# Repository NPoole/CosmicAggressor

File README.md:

# CosmicAggressor

Badge style 'Space Invaders' clone based on the stacked-FR4 construction technique.<br/>
Processor is 32u4, LEDs are APA-102-2020 6-pin

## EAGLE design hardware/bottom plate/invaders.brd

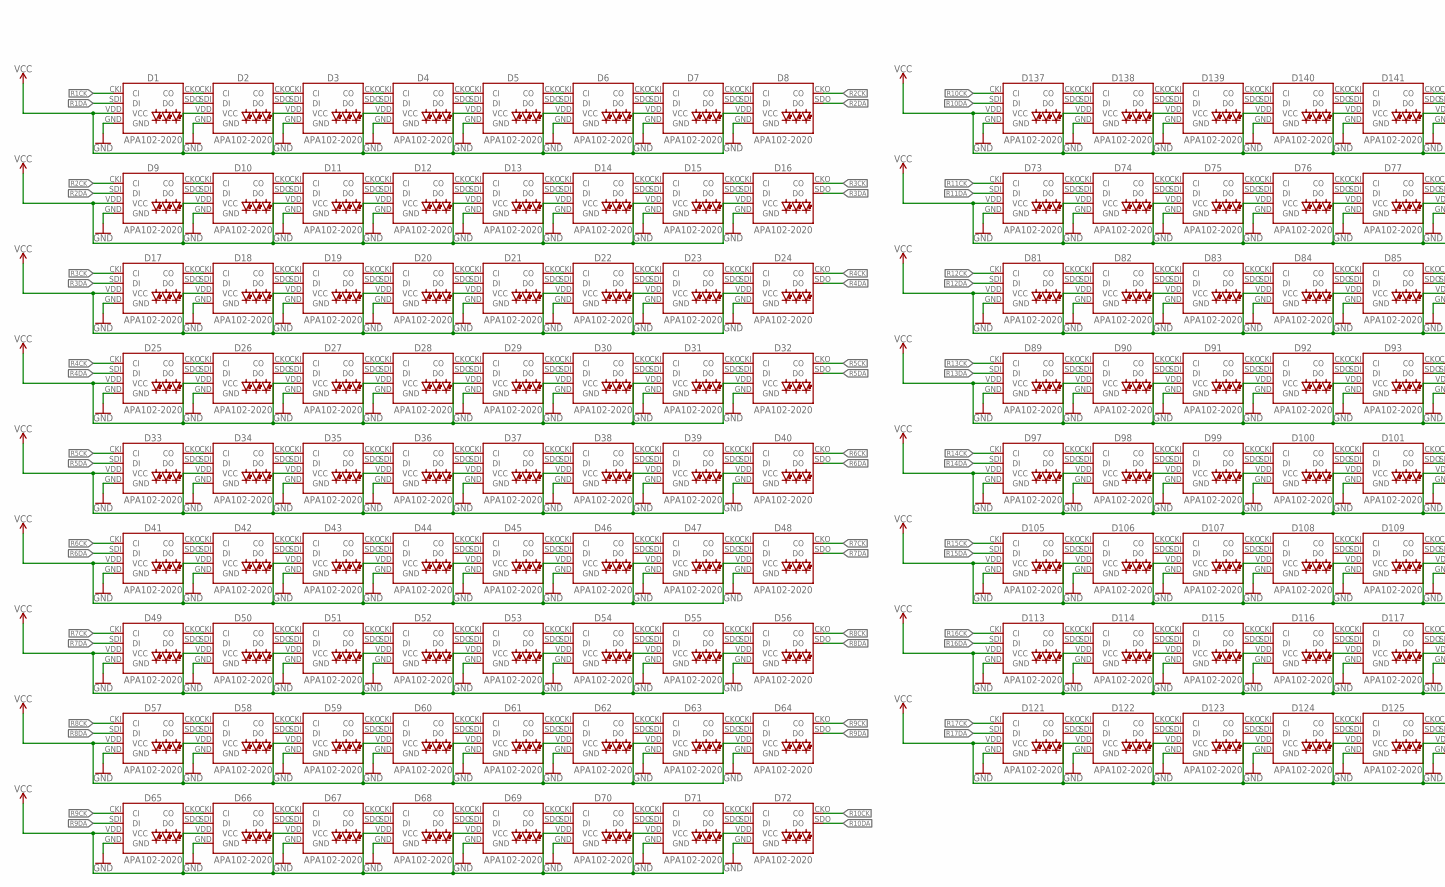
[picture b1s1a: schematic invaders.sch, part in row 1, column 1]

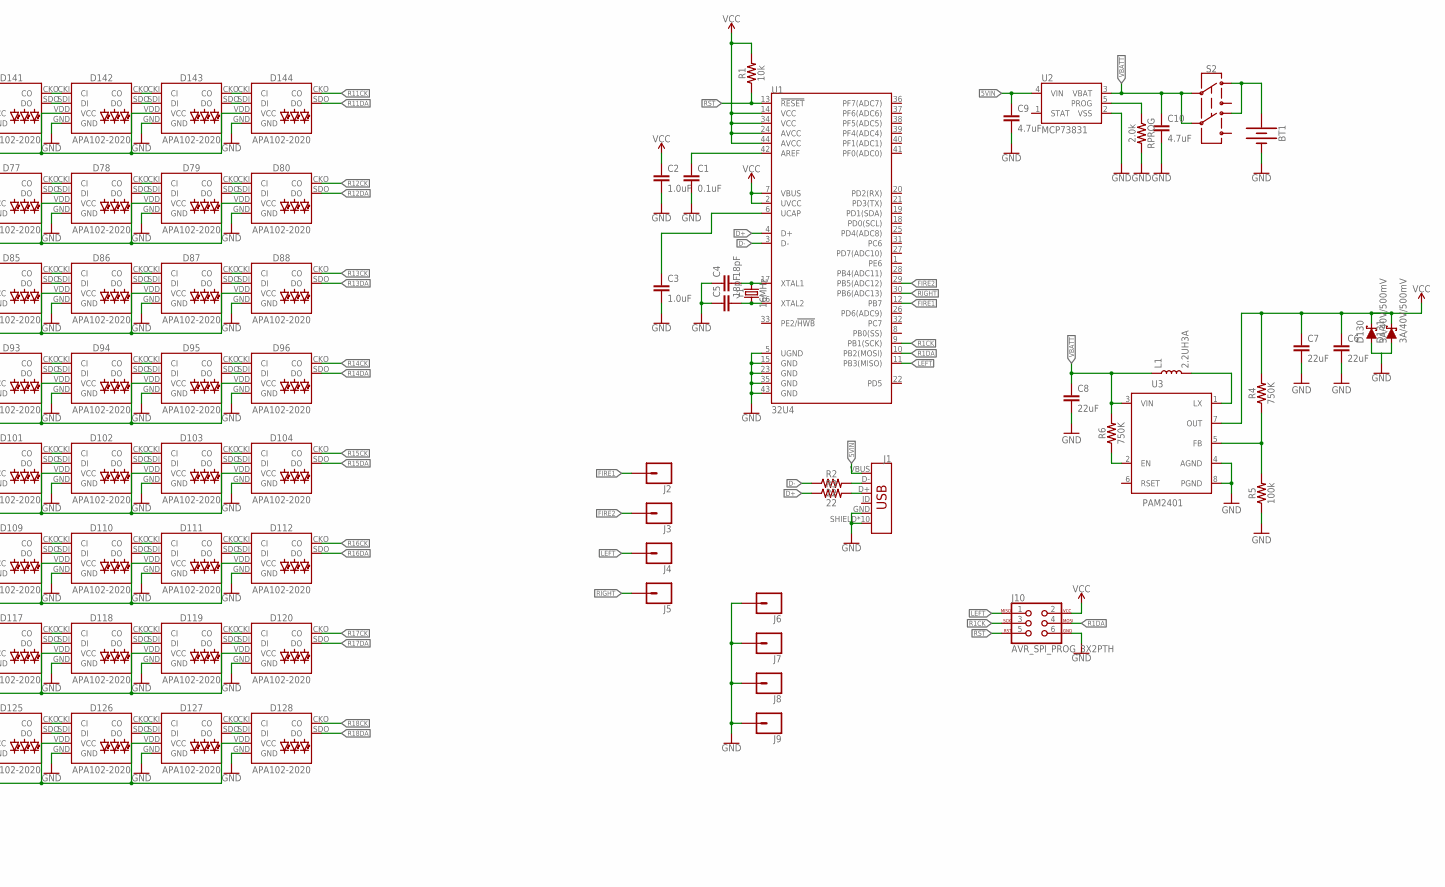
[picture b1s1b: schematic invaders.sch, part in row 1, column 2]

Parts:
BT1: BATTERY-18650; BATTERY_18650-HOLDER
C1: 0.1uF; 0603
C2, C3: 1.0uF; 0603
C4, C5: 18pF; 0603
C6, C7, C8: 22uF; 0805
C9, C10: 4.7uF; 0603
D1, D2, D3, D4, D5, D6, D7, D8, D9, D10, D11, D12, D13, D14, D15, D16, D17, D18, D19, D20, D21, D22, D23, D24, D25, D26, D27, D28, D29, D30, D31, D32, D33, D34, D35, D36, D37, D38, D39, D40, D41, D42, D43, D44, D45, D46, D47, D48, D49, D50, D51, D52, D53, D54, D55, D56, D57, D58, D59, D60, D61, D62, D63, D64, D65, D66, D67, D68, D69, D70, D71, D72, D73, D74, D75, D76, D77, D78, D79, D80, D81, D82, D83, D84, D85, D86, D87, D88, D89, D90, D91, D92, D93, D94, D95, D96, D97, D98, D99, D100, D101, D102, D103, D104, D105, D106, D107, D108, D109, D110, D111, D112, D113, D114, D115, D116, D117, D118, D119, D120, D121, D122, D123, D124, D125, D126, D127, D128, D137, D138, D139, D140, D141, D142, D143, D144: APA102-2020
D130, D131: 3A/40V/500mV; SMA-DIODE
J1: USB_MICRO-B_HALF_PTH_MILL; USB-MICROB-PTH-MILL
J2, J3, J4, J5, J6, J7, J8, J9: CONN_01PTH_NO_SILK_KIT; 1X01NS_KIT
J10: AVR_SPI_PROG_3X2PTH; 2X3
L1: 2.2UH3A; INDUCTOR_4X4MM
R1: 10k; 0603@1
R2, R3: 22; 0603@1
R4, R6: 750K; 0603
R5: 100k; 0603
RPROG: 2.0k; 0603
S2: SWITCH-DPDT-SMD-AYZ0202; SWITCH_DPDT_SMD_AYZ0202
U1: 32U4; QFN-44-NOPAD_1:1-LESS_PASTE
U2: MCP73831; SOT23-5
U3: PAM2401; MSOP8
Y1: 16MHz; CRYSTAL-SMD-5X3.2-4PAD

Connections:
D+: R3.1, U1.4 (D+)
D-: R2.1, U1.3 (D-)
FIRE1: J2.1, U1.12 (PB7)
FIRE2: J3.1, U1.29 (PB5(ADC12))
GND: BT1.GND@1 (-), C1.2, C2.2, C3.2, C4.1, C5.1, C6.2, C7.2, C8.2, C9.2, C10.2, D1.GND, D2.GND, D3.GND, D4.GND, D5.GND, D6.GND, D7.GND, D8.GND, D9.GND, D10.GND, D11.GND, D12.GND, D13.GND, D14.GND, D15.GND, D16.GND, D17.GND, D18.GND, D19.GND, D20.GND, D21.GND, D22.GND, D23.GND, D24.GND, D25.GND, D26.GND, D27.GND, D28.GND, D29.GND, D30.GND, D31.GND, D32.GND, D33.GND, D34.GND, D35.GND, D36.GND, D37.GND, D38.GND, D39.GND, D40.GND, D41.GND, D42.GND, D43.GND, D44.GND, D45.GND, D46.GND, D47.GND, D48.GND, D49.GND, D50.GND, D51.GND, D52.GND, D53.GND, D54.GND, D55.GND, D56.GND, D57.GND, D58.GND, D59.GND, D60.GND, D61.GND, D62.GND, D63.GND, D64.GND, D65.GND, D66.GND, D67.GND, D68.GND, D69.GND, D70.GND, D71.GND, D72.GND, D73.GND, D74.GND, D75.GND, D76.GND, D77.GND, D78.GND, D79.GND, D80.GND, D81.GND, D82.GND, D83.GND, D84.GND, D85.GND, D86.GND, D87.GND, D88.GND, D89.GND, D90.GND, D91.GND, D92.GND, D93.GND, D94.GND, D95.GND, D96.GND, D97.GND, D98.GND, D99.GND, D100.GND, D101.GND, D102.GND, D103.GND, D104.GND, D105.GND, D106.GND, D107.GND, D108.GND, D109.GND, D110.GND, D111.GND, D112.GND, D113.GND, D114.GND, D115.GND, D116.GND, D117.GND, D118.GND, D119.GND, D120.GND, D121.GND, D122.GND, D123.GND, D124.GND, D125.GND, D126.GND, D127.GND, D128.GND, D130.A, D131.A, D137.GND, D138.GND, D139.GND, D140.GND, D141.GND, D142.GND, D143.GND, D144.GND, J1.GND, J1.SHIELD, J1.SHIELD2 (SHIELD), J1.SHIELD3 (SHIELD), J1.SHIELD4 (SHIELD), J1.SHIELD5 (SHIELD), J1.SHIELD6 (SHIELD), J1.SHIELD7 (SHIELD), J1.SHIELD8 (SHIELD), J1.SHIELD9 (SHIELD), J1.SHIELD10 (SHIELD), J6.1, J7.1, J8.1, J9.1, J10.6, R5.1, RPROG.2, U1.5 (UGND), U1.15 (GND), U1.23 (GND), U1.35 (GND), U1.43 (GND), U2.2 (VSS), U3.4 (AGND), U3.8 (PGND)
LEFT: J4.1, J10.1, U1.11 (PB3(MISO))
unnamed: D73.CKO (CO), D74.CKI (CI)
unnamed: D73.SDO (DO), D74.SDI (DI)
unnamed: D1.CKO (CO), D2.CKI (CI)
unnamed: D1.SDO (DO), D2.SDI (DI)
unnamed: D2.CKO (CO), D3.CKI (CI)
unnamed: D2.SDO (DO), D3.SDI (DI)
unnamed: D3.CKO (CO), D4.CKI (CI)
unnamed: D3.SDO (DO), D4.SDI (DI)
unnamed: D4.CKO (CO), D5.CKI (CI)
unnamed: D4.SDO (DO), D5.SDI (DI)
unnamed: D5.CKO (CO), D6.CKI (CI)
unnamed: D5.SDO (DO), D6.SDI (DI)
unnamed: D6.CKO (CO), D7.CKI (CI)
unnamed: D6.SDO (DO), D7.SDI (DI)
unnamed: D7.CKO (CO), D8.CKI (CI)
unnamed: D7.SDO (DO), D8.SDI (DI)
unnamed: D74.CKO (CO), D75.CKI (CI)
unnamed: D74.SDO (DO), D75.SDI (DI)
unnamed: D75.CKO (CO), D76.CKI (CI)
unnamed: D75.SDO (DO), D76.SDI (DI)
unnamed: D9.CKO (CO), D10.CKI (CI)
unnamed: D9.SDO (DO), D10.SDI (DI)
unnamed: D10.CKO (CO), D11.CKI (CI)
unnamed: D10.SDO (DO), D11.SDI (DI)
unnamed: D11.CKO (CO), D12.CKI (CI)
unnamed: D11.SDO (DO), D12.SDI (DI)
unnamed: D12.CKO (CO), D13.CKI (CI)
unnamed: D12.SDO (DO), D13.SDI (DI)
unnamed: D13.CKO (CO), D14.CKI (CI)
unnamed: D13.SDO (DO), D14.SDI (DI)
unnamed: D14.CKO (CO), D15.CKI (CI)
unnamed: D14.SDO (DO), D15.SDI (DI)
unnamed: D15.CKO (CO), D16.CKI (CI)
unnamed: D15.SDO (DO), D16.SDI (DI)
unnamed: D76.CKO (CO), D77.CKI (CI)
unnamed: D76.SDO (DO), D77.SDI (DI)
unnamed: D77.CKO (CO), D78.CKI (CI)
unnamed: D77.SDO (DO), D78.SDI (DI)
unnamed: D17.CKO (CO), D18.CKI (CI)
unnamed: D17.SDO (DO), D18.SDI (DI)
unnamed: D18.CKO (CO), D19.CKI (CI)
unnamed: D18.SDO (DO), D19.SDI (DI)
unnamed: D19.CKO (CO), D20.CKI (CI)
unnamed: D19.SDO (DO), D20.SDI (DI)
unnamed: D20.CKO (CO), D21.CKI (CI)
unnamed: D20.SDO (DO), D21.SDI (DI)
unnamed: D21.CKO (CO), D22.CKI (CI)
unnamed: D21.SDO (DO), D22.SDI (DI)
unnamed: D22.CKO (CO), D23.CKI (CI)
unnamed: D22.SDO (DO), D23.SDI (DI)
unnamed: D23.CKO (CO), D24.CKI (CI)
unnamed: D23.SDO (DO), D24.SDI (DI)
unnamed: D78.CKO (CO), D79.CKI (CI)
unnamed: D78.SDO (DO), D79.SDI (DI)
unnamed: D79.CKO (CO), D80.CKI (CI)
unnamed: D79.SDO (DO), D80.SDI (DI)
unnamed: D25.CKO (CO), D26.CKI (CI)
unnamed: D25.SDO (DO), D26.SDI (DI)
unnamed: D26.CKO (CO), D27.CKI (CI)
unnamed: D26.SDO (DO), D27.SDI (DI)
unnamed: D27.CKO (CO), D28.CKI (CI)
unnamed: D27.SDO (DO), D28.SDI (DI)
unnamed: D28.CKO (CO), D29.CKI (CI)
unnamed: D28.SDO (DO), D29.SDI (DI)
unnamed: D29.CKO (CO), D30.CKI (CI)
unnamed: D29.SDO (DO), D30.SDI (DI)
unnamed: D30.CKO (CO), D31.CKI (CI)
unnamed: D30.SDO (DO), D31.SDI (DI)
unnamed: D31.CKO (CO), D32.CKI (CI)
unnamed: D31.SDO (DO), D32.SDI (DI)
unnamed: D39.CKO (CO), D40.CKI (CI)
unnamed: D39.SDO (DO), D40.SDI (DI)
unnamed: D38.SDO (DO), D39.SDI (DI)
unnamed: D38.CKO (CO), D39.CKI (CI)
unnamed: D37.SDO (DO), D38.SDI (DI)
unnamed: D37.CKO (CO), D38.CKI (CI)
unnamed: D36.SDO (DO), D37.SDI (DI)
unnamed: D36.CKO (CO), D37.CKI (CI)
unnamed: D35.SDO (DO), D36.SDI (DI)
unnamed: D35.CKO (CO), D36.CKI (CI)
unnamed: D34.SDO (DO), D35.SDI (DI)
unnamed: D34.CKO (CO), D35.CKI (CI)
unnamed: D33.CKO (CO), D34.CKI (CI)
unnamed: D33.SDO (DO), D34.SDI (DI)
unnamed: D81.CKO (CO), D82.CKI (CI)
unnamed: D81.SDO (DO), D82.SDI (DI)
unnamed: D82.CKO (CO), D83.CKI (CI)
unnamed: D82.SDO (DO), D83.SDI (DI)
unnamed: D83.CKO (CO), D84.CKI (CI)
unnamed: D83.SDO (DO), D84.SDI (DI)
unnamed: D84.CKO (CO), D85.CKI (CI)
unnamed: D84.SDO (DO), D85.SDI (DI)
unnamed: D85.CKO (CO), D86.CKI (CI)
unnamed: D85.SDO (DO), D86.SDI (DI)
unnamed: D41.CKO (CO), D42.CKI (CI)
unnamed: D41.SDO (DO), D42.SDI (DI)
unnamed: D42.CKO (CO), D43.CKI (CI)
unnamed: D42.SDO (DO), D43.SDI (DI)
unnamed: D43.CKO (CO), D44.CKI (CI)
unnamed: D43.SDO (DO), D44.SDI (DI)
unnamed: D44.CKO (CO), D45.CKI (CI)
unnamed: D44.SDO (DO), D45.SDI (DI)
unnamed: D45.SDO (DO), D46.SDI (DI)
unnamed: D45.CKO (CO), D46.CKI (CI)
unnamed: D46.CKO (CO), D47.CKI (CI)
unnamed: D46.SDO (DO), D47.SDI (DI)
unnamed: D47.CKO (CO), D48.CKI (CI)
unnamed: D47.SDO (DO), D48.SDI (DI)
unnamed: D86.CKO (CO), D87.CKI (CI)
unnamed: D86.SDO (DO), D87.SDI (DI)
unnamed: D55.SDO (DO), D56.SDI (DI)
unnamed: D55.CKO (CO), D56.CKI (CI)
unnamed: D54.CKO (CO), D55.CKI (CI)
unnamed: D54.SDO (DO), D55.SDI (DI)
unnamed: D53.SDO (DO), D54.SDI (DI)
unnamed: D53.CKO (CO), D54.CKI (CI)
unnamed: D52.SDO (DO), D53.SDI (DI)
unnamed: D52.CKO (CO), D53.CKI (CI)
unnamed: D51.SDO (DO), D52.SDI (DI)
unnamed: D51.CKO (CO), D52.CKI (CI)
unnamed: D50.CKO (CO), D51.CKI (CI)
unnamed: D50.SDO (DO), D51.SDI (DI)
unnamed: D49.SDO (DO), D50.SDI (DI)
unnamed: D49.CKO (CO), D50.CKI (CI)
unnamed: D87.CKO (CO), D88.CKI (CI)
unnamed: D87.SDO (DO), D88.SDI (DI)
unnamed: D89.CKO (CO), D90.CKI (CI)
unnamed: D89.SDO (DO), D90.SDI (DI)
unnamed: D57.CKO (CO), D58.CKI (CI)
unnamed: D57.SDO (DO), D58.SDI (DI)
unnamed: D58.SDO (DO), D59.SDI (DI)
unnamed: D58.CKO (CO), D59.CKI (CI)
unnamed: D59.CKO (CO), D60.CKI (CI)
unnamed: D59.SDO (DO), D60.SDI (DI)
unnamed: D60.CKO (CO), D61.CKI (CI)
unnamed: D60.SDO (DO), D61.SDI (DI)
unnamed: D61.CKO (CO), D62.CKI (CI)
unnamed: D61.SDO (DO), D62.SDI (DI)
unnamed: D62.SDO (DO), D63.SDI (DI)
unnamed: D62.CKO (CO), D63.CKI (CI)
unnamed: D63.CKO (CO), D64.CKI (CI)
unnamed: D63.SDO (DO), D64.SDI (DI)
unnamed: D90.CKO (CO), D91.CKI (CI)
unnamed: D90.SDO (DO), D91.SDI (DI)
unnamed: D91.CKO (CO), D92.CKI (CI)
unnamed: D91.SDO (DO), D92.SDI (DI)
unnamed: D65.CKO (CO), D66.CKI (CI)
unnamed: D65.SDO (DO), D66.SDI (DI)
unnamed: D66.CKO (CO), D67.CKI (CI)
unnamed: D66.SDO (DO), D67.SDI (DI)
unnamed: D67.CKO (CO), D68.CKI (CI)
unnamed: D67.SDO (DO), D68.SDI (DI)
unnamed: D68.CKO (CO), D69.CKI (CI)
unnamed: D68.SDO (DO), D69.SDI (DI)
unnamed: D69.CKO (CO), D70.CKI (CI)
unnamed: D69.SDO (DO), D70.SDI (DI)
unnamed: D70.CKO (CO), D71.CKI (CI)
unnamed: D70.SDO (DO), D71.SDI (DI)
unnamed: D71.CKO (CO), D72.CKI (CI)
unnamed: D71.SDO (DO), D72.SDI (DI)
unnamed: D137.CKO (CO), D138.CKI (CI)
unnamed: D137.SDO (DO), D138.SDI (DI)
unnamed: D92.CKO (CO), D93.CKI (CI)
unnamed: D92.SDO (DO), D93.SDI (DI)
unnamed: D93.CKO (CO), D94.CKI (CI)
unnamed: D93.SDO (DO), D94.SDI (DI)
unnamed: D94.CKO (CO), D95.CKI (CI)
unnamed: D94.SDO (DO), D95.SDI (DI)
unnamed: D95.CKO (CO), D96.CKI (CI)
unnamed: D95.SDO (DO), D96.SDI (DI)
unnamed: D97.CKO (CO), D98.CKI (CI)
unnamed: D97.SDO (DO), D98.SDI (DI)
unnamed: D98.CKO (CO), D99.CKI (CI)
unnamed: D98.SDO (DO), D99.SDI (DI)
unnamed: D99.CKO (CO), D100.CKI (CI)
unnamed: D99.SDO (DO), D100.SDI (DI)
unnamed: D100.CKO (CO), D101.CKI (CI)
unnamed: D100.SDO (DO), D101.SDI (DI)
unnamed: D101.CKO (CO), D102.CKI (CI)
unnamed: D101.SDO (DO), D102.SDI (DI)
unnamed: D102.CKO (CO), D103.CKI (CI)
unnamed: D102.SDO (DO), D103.SDI (DI)
unnamed: D103.CKO (CO), D104.CKI (CI)
unnamed: D103.SDO (DO), D104.SDI (DI)
unnamed: D111.CKO (CO), D112.CKI (CI)
unnamed: D111.SDO (DO), D112.SDI (DI)
unnamed: D110.SDO (DO), D111.SDI (DI)
unnamed: D110.CKO (CO), D111.CKI (CI)
unnamed: D109.SDO (DO), D110.SDI (DI)
unnamed: D109.CKO (CO), D110.CKI (CI)
unnamed: D108.SDO (DO), D109.SDI (DI)
unnamed: D108.CKO (CO), D109.CKI (CI)
unnamed: D107.SDO (DO), D108.SDI (DI)
unnamed: D107.CKO (CO), D108.CKI (CI)
unnamed: D106.SDO (DO), D107.SDI (DI)
unnamed: D106.CKO (CO), D107.CKI (CI)
unnamed: D105.CKO (CO), D106.CKI (CI)
unnamed: D105.SDO (DO), D106.SDI (DI)
unnamed: D113.CKO (CO), D114.CKI (CI)
unnamed: D113.SDO (DO), D114.SDI (DI)
unnamed: D114.CKO (CO), D115.CKI (CI)
unnamed: D114.SDO (DO), D115.SDI (DI)
unnamed: D115.CKO (CO), D116.CKI (CI)
unnamed: D115.SDO (DO), D116.SDI (DI)
unnamed: D116.CKO (CO), D117.CKI (CI)
unnamed: D116.SDO (DO), D117.SDI (DI)
unnamed: D117.SDO (DO), D118.SDI (DI)
unnamed: D117.CKO (CO), D118.CKI (CI)
unnamed: D118.CKO (CO), D119.CKI (CI)
unnamed: D118.SDO (DO), D119.SDI (DI)
unnamed: D119.CKO (CO), D120.CKI (CI)
unnamed: D119.SDO (DO), D120.SDI (DI)
unnamed: D127.SDO (DO), D128.SDI (DI)
unnamed: D127.CKO (CO), D128.CKI (CI)
unnamed: D126.CKO (CO), D127.CKI (CI)
unnamed: D126.SDO (DO), D127.SDI (DI)
unnamed: D125.SDO (DO), D126.SDI (DI)
unnamed: D125.CKO (CO), D126.CKI (CI)
unnamed: D124.SDO (DO), D125.SDI (DI)
unnamed: D124.CKO (CO), D125.CKI (CI)
unnamed: D123.SDO (DO), D124.SDI (DI)
unnamed: D123.CKO (CO), D124.CKI (CI)
unnamed: D122.CKO (CO), D123.CKI (CI)
unnamed: D122.SDO (DO), D123.SDI (DI)
unnamed: D121.SDO (DO), D122.SDI (DI)
unnamed: D121.CKO (CO), D122.CKI (CI)
unnamed: C1.1, U1.42 (AREF)
unnamed: C4.2, U1.17 (XTAL1), Y1.3 (2)
unnamed: J10.5, R1.1, U1.13 (!RESET)
unnamed: C5.2, U1.16 (XTAL2), Y1.1
unnamed: C3.1, U1.6 (UCAP)
unnamed: J1.D+, R3.2
unnamed: J1.D-, R2.2
unnamed: D138.CKO (CO), D139.CKI (CI)
unnamed: D138.SDO (DO), D139.SDI (DI)
unnamed: D139.CKO (CO), D140.CKI (CI)
unnamed: D139.SDO (DO), D140.SDI (DI)
unnamed: D140.CKO (CO), D141.CKI (CI)
unnamed: D140.SDO (DO), D141.SDI (DI)
unnamed: D141.CKO (CO), D142.CKI (CI)
unnamed: D141.SDO (DO), D142.SDI (DI)
unnamed: D142.CKO (CO), D143.CKI (CI)
unnamed: D142.SDO (DO), D143.SDI (DI)
unnamed: D143.CKO (CO), D144.CKI (CI)
unnamed: D143.SDO (DO), D144.SDI (DI)
unnamed: BT1.PWR@1 (+), S2.1, S2.4
unnamed: C8.1, C10.1, L1.P$1 (1), R6.2, S2.2, S2.5, U2.3 (VBAT), U3.3 (VIN)
unnamed: L1.P$2 (2), U3.1 (LX)
unnamed: R4.1, R5.2, U3.5 (FB)
unnamed: R6.1, U3.2 (EN)
unnamed: RPROG.1, U2.5 (PROG)
R1CK: D1.CKI (CI), J10.3, U1.9 (PB1(SCK))
R1DA: D1.SDI (DI), J10.4, U1.10 (PB2(MOSI))
R2CK: D8.CKO (CO), D9.CKI (CI)
R2DA: D8.SDO (DO), D9.SDI (DI)
R3CK: D16.CKO (CO), D17.CKI (CI)
R3DA: D16.SDO (DO), D17.SDI (DI)
R4CK: D24.CKO (CO), D25.CKI (CI)
R4DA: D24.SDO (DO), D25.SDI (DI)
R5CK: D32.CKO (CO), D33.CKI (CI)
R5DA: D32.SDO (DO), D33.SDI (DI)
R6CK: D40.CKO (CO), D41.CKI (CI)
R6DA: D40.SDO (DO), D41.SDI (DI)
R7CK: D48.CKO (CO), D49.CKI (CI)
R7DA: D48.SDO (DO), D49.SDI (DI)
R8CK: D56.CKO (CO), D57.CKI (CI)
R8DA: D56.SDO (DO), D57.SDI (DI)
R9CK: D64.CKO (CO), D65.CKI (CI)
R9DA: D64.SDO (DO), D65.SDI (DI)
R10CK: D72.CKO (CO), D137.CKI (CI)
R10DA: D72.SDO (DO), D137.SDI (DI)
R11CK: D73.CKI (CI), D144.CKO (CO)
R11DA: D73.SDI (DI), D144.SDO (DO)
R12CK: D80.CKO (CO), D81.CKI (CI)
R12DA: D80.SDO (DO), D81.SDI (DI)
R13CK: D88.CKO (CO), D89.CKI (CI)
R13DA: D88.SDO (DO), D89.SDI (DI)
R14CK: D96.CKO (CO), D97.CKI (CI)
R14DA: D96.SDO (DO), D97.SDI (DI)
R15CK: D104.CKO (CO), D105.CKI (CI)
R15DA: D104.SDO (DO), D105.SDI (DI)
R16CK: D112.CKO (CO), D113.CKI (CI)
R16DA: D112.SDO (DO), D113.SDI (DI)
R17CK: D120.CKO (CO), D121.CKI (CI)
R17DA: D120.SDO (DO), D121.SDI (DI)
R18CK: D128.CKO (CO)
R18DA: D128.SDO (DO)
RIGHT: J5.1, U1.30 (PB6(ADC13))

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
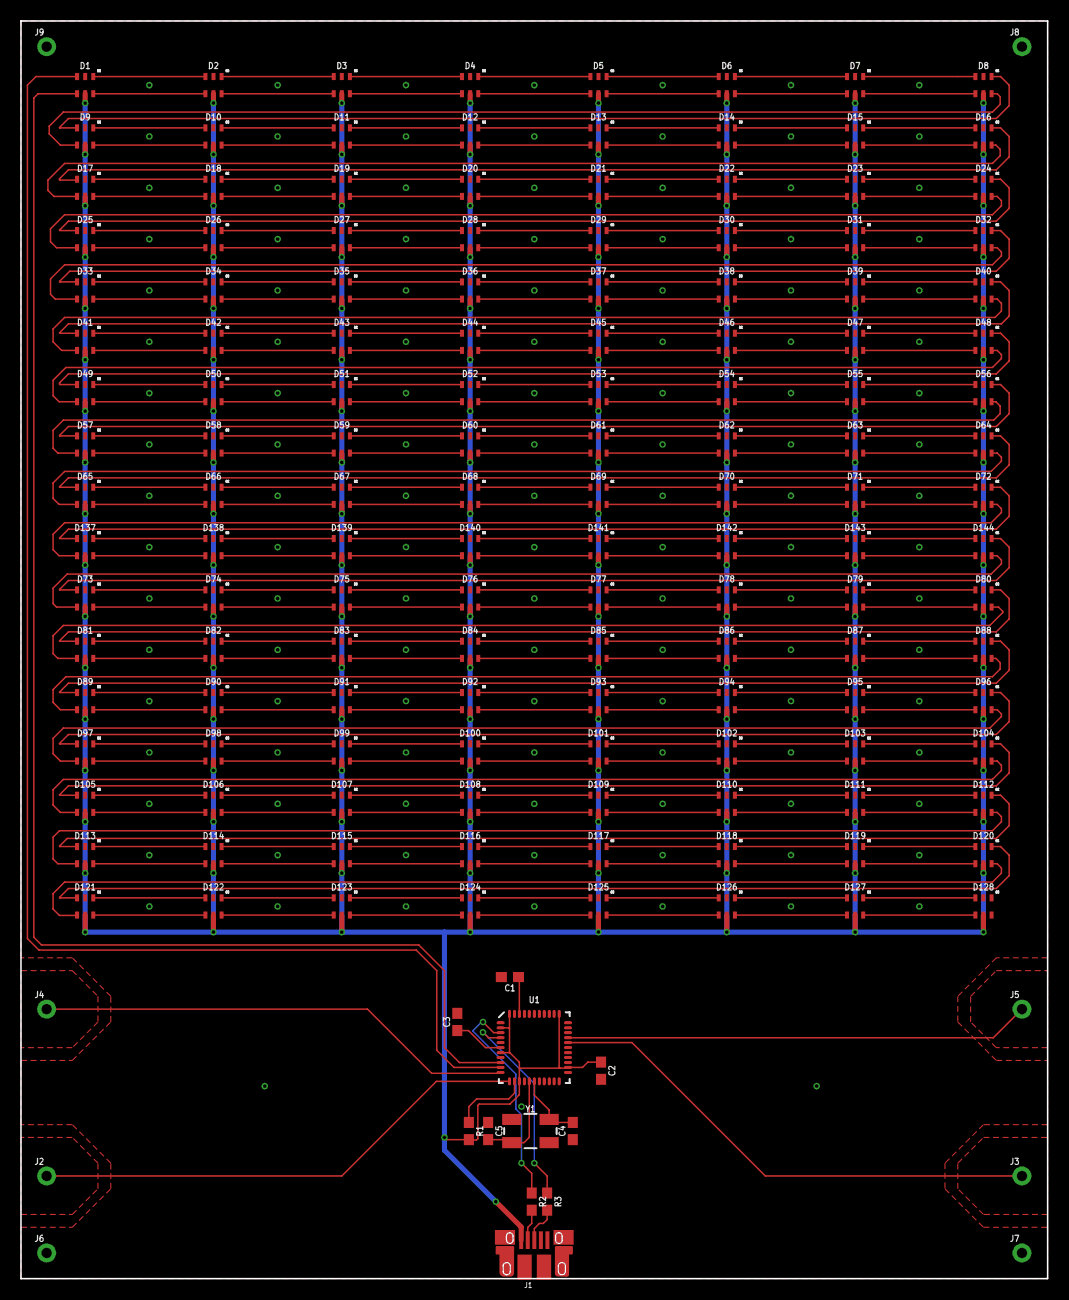
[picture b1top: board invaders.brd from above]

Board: 2 copper layers, 101.6 x 124.5 mm, 155 parts (0 on the bottom side), 287 nets.

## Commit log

2019-10-28 Tested Hardware
    AOK
    Also proof of concept firmware
2019-10-29 Basic gameplay
2019-11-01 Add 18650 and LiPo circuit
2019-11-14 Aggressor Firmware Update
2019-11-18 Fast 5
    5 levels
    5 lives
    5ever
2019-11-20 Add images for the readme

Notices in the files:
parts and their libraries:
SparkFun-LED: Licensing: Creative Commons ShareAlike 4.0 International - https://creativecommons.org/licenses/by-sa/4.0
